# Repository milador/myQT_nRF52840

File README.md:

# myQT_nRF52840

myQT nRF52840 is a development board based on Nordic nRF52840 Bluetooth module in Seeeduino XIAO/QT py form factor.

## myQT nRF52840 Arduino IDE Setup

Please visit [milador-arduino](https://github.com/milador/milador-arduino/blob/main/boards/README.md) github page to find out about installation process.

## myQT nRF52840 Pinout

## myQT nRF52840 PCB Design 

## myQT nRF52840 3D Model

## License

Designed by milador based on Adafruit QT py design.

Creative Commons Attribution/Share-Alike, all text above must be included in any redistribution. Please read license.txt for additional details.

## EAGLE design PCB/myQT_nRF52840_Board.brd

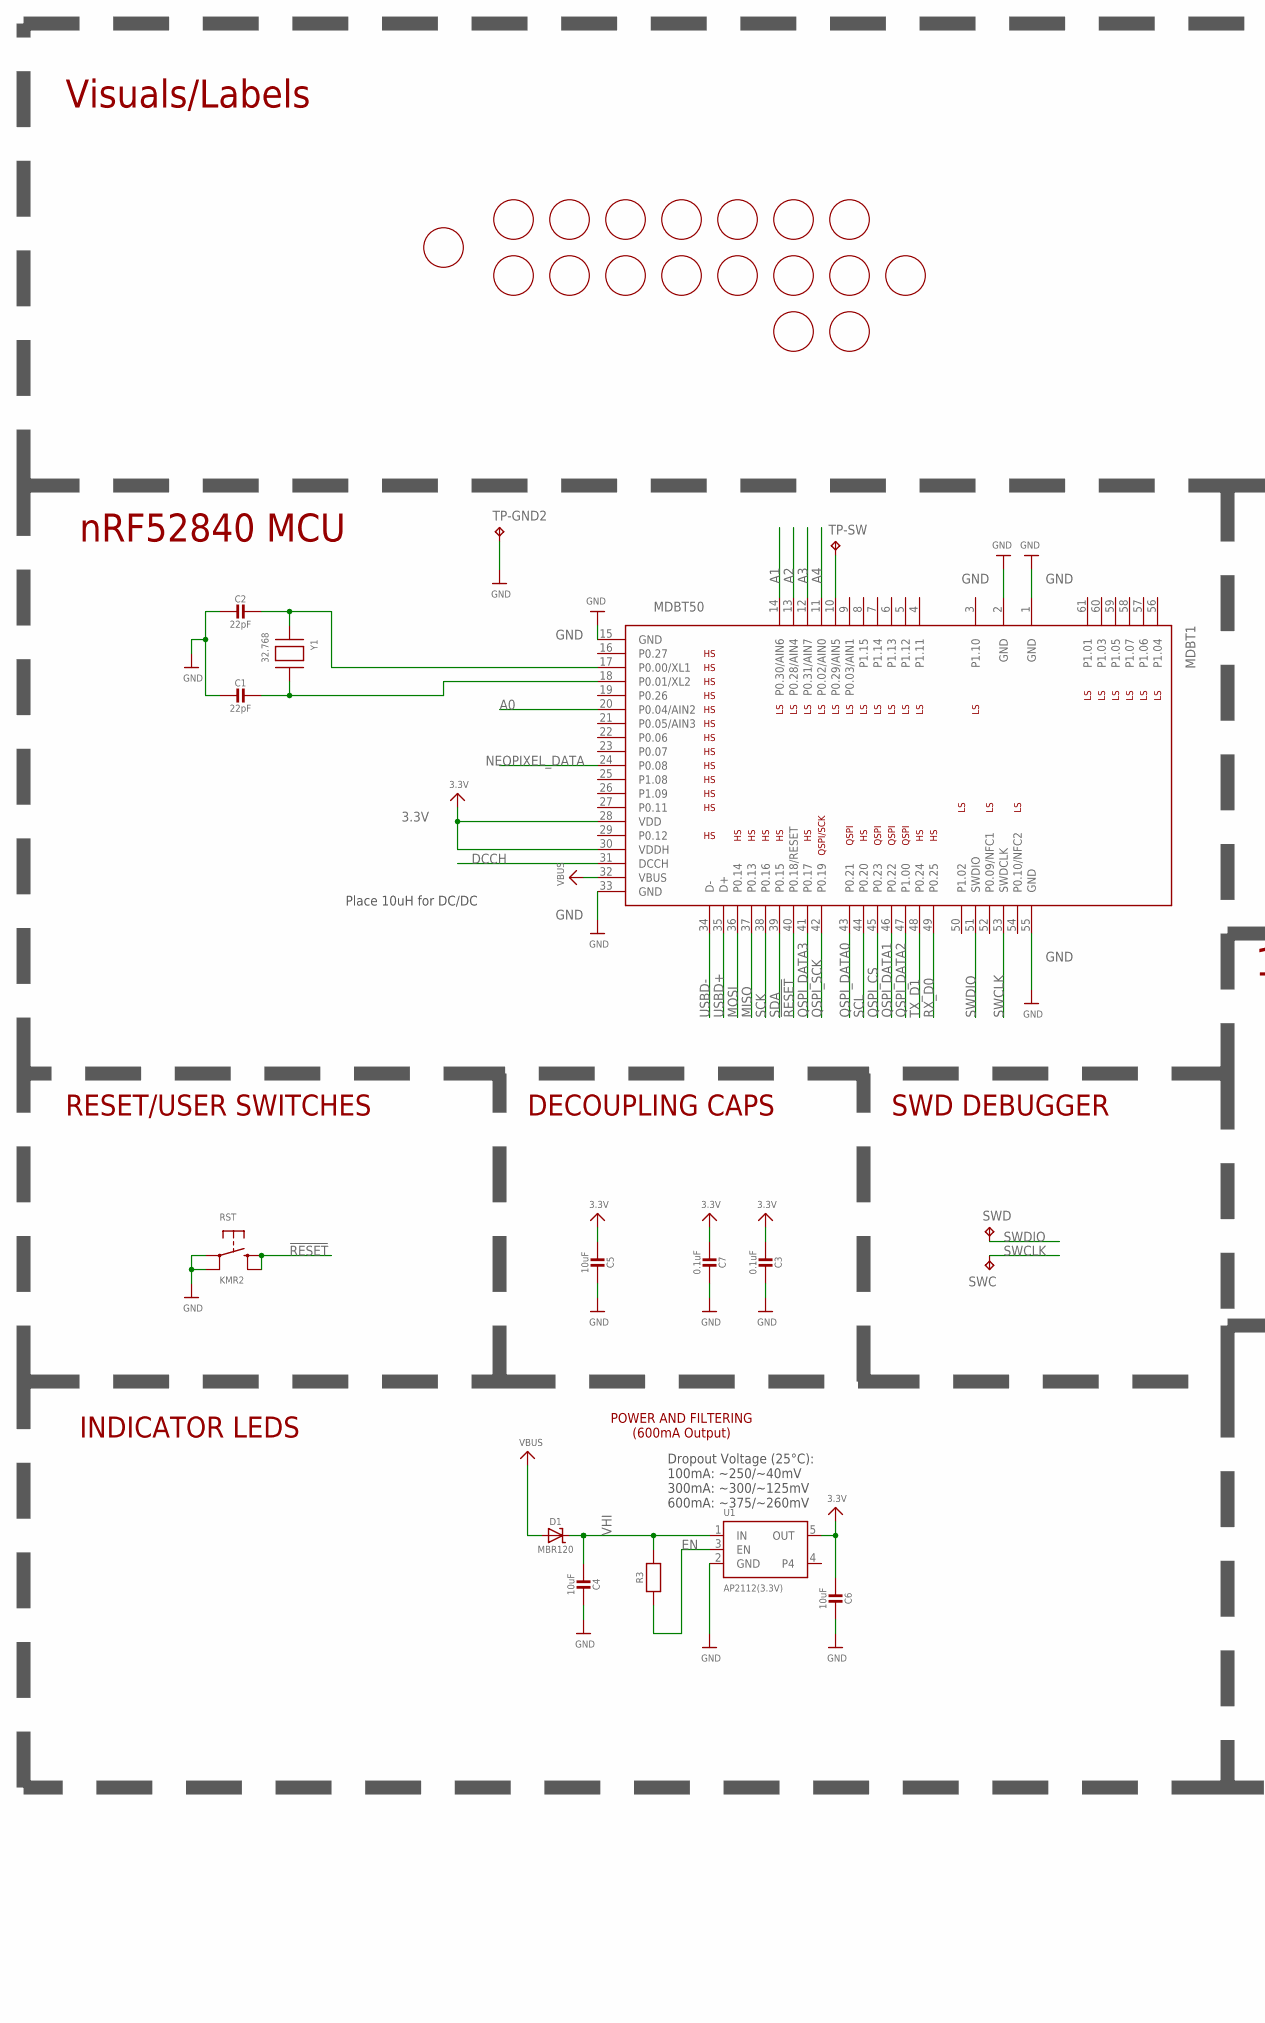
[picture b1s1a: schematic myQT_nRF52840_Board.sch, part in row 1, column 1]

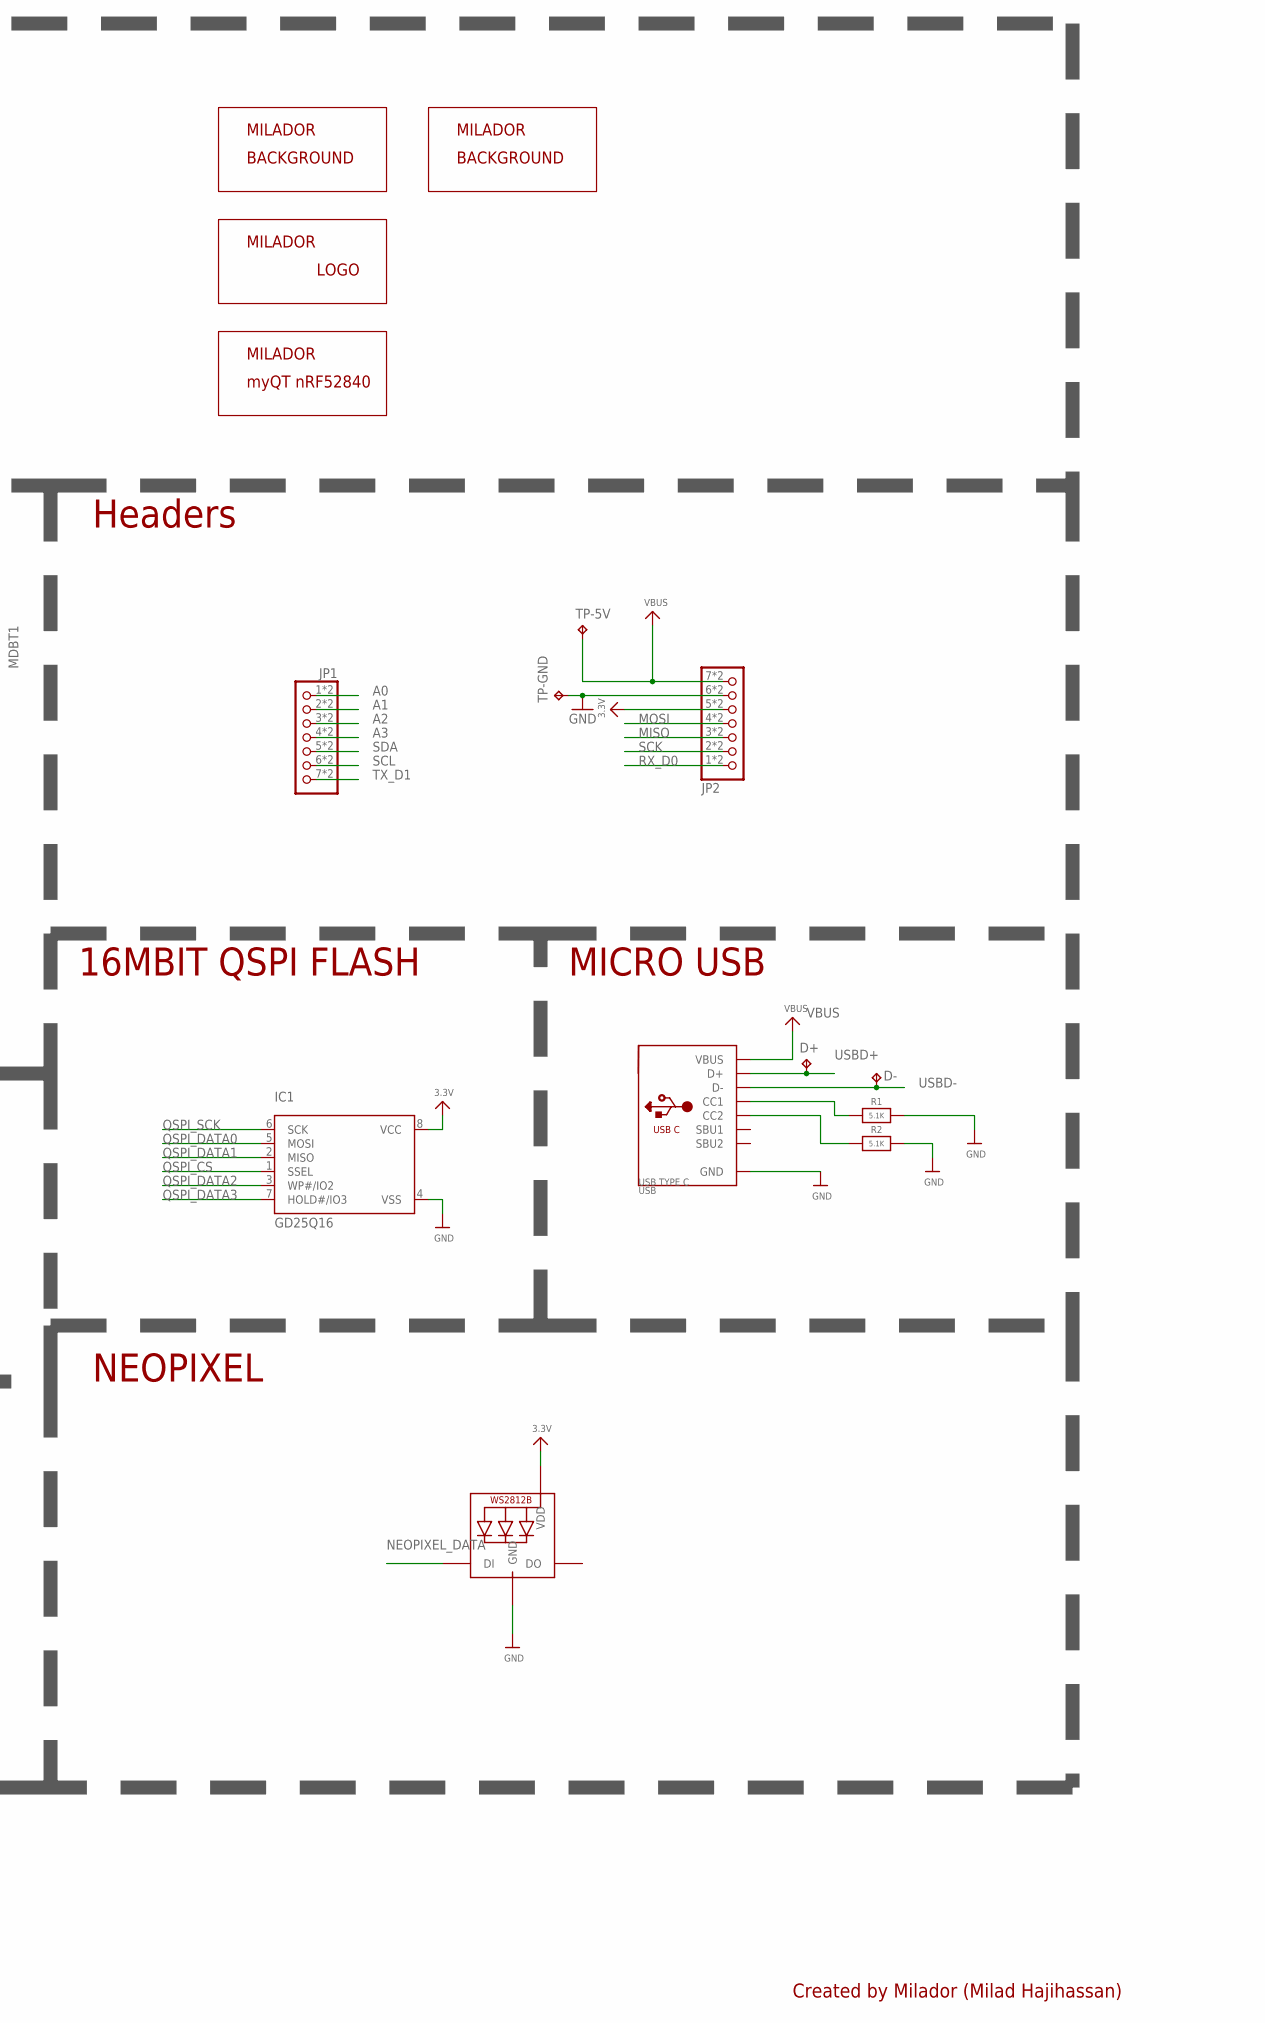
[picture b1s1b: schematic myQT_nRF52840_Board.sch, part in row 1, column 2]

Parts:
C1, C2: 22pF; 0603-MP
C3, C7: 0.1uF; 0603-NO
C4, C5, C6: 10uF; 0805-NO
D1: MBR120; SOD-123
D+: TESTPAD_TPTP10R; TESTPAD_TP10R
D-: TESTPAD_TPTP10R; TESTPAD_TP10R
IC1: GD25Q16; USON8
JP1, JP2: HEADER-1X7_CASTEL; 1X07_CASTEL
LED: WS2812B_SK6805_1515; SK6805_1515
MDBT1: MDBT50
R1, R2: 5.1K; 0402-NO
R3: 10K; 0603-NO
RST: KMR2; BTN_KMR2_4.6X2.8
SWC: TESTPAD_TPTP13R; TESTPAD_TP13R
SWD: TESTPAD_TPTP13R; TESTPAD_TP13R
TP-5V: TESTPAD_TPB1,27; TESTPAD_B1,27
TP-GND: TESTPAD_TPB1,27; TESTPAD_B1,27
TP-GND2: TESTPAD_TPTP06R; TESTPAD_TP06R
TP-SW: TESTPAD_TPTP06R; TESTPAD_TP06R
U1: AP2112(3.3V); SOT23-5
U$6: MILADOR-PIN-NAME-A0; PIN-A0
U$7: MILADOR-PIN-NAME-5V; PIN-5V
U$10: MILADOR-PIN-NAME-GND; PIN-GND
U$12: MILADOR-PIN-NAME-3V; PIN-3V
U$14: MILADOR-PIN-NAME-MO2; PIN-MO2
U$18: MILADOR-PIN-NAME-MI2; PIN-MI2
U$20: MILADOR-PIN-NAME-SCK2; PIN-SCK2
U$24: MILADOR-PIN-NAME-RX; PIN-RX
U$25: MILADOR-PIN-NAME-A1; PIN-A1
U$26: MILADOR-PIN-NAME-A2; PIN-A2
U$27: MILADOR-PIN-NAME-A3; PIN-A3
U$28: MILADOR-PIN-NAME-TX; PIN-TX
U$29: MILADOR-PIN-NAME-SDA2; PIN-SDA2
U$33: MILADOR-PIN-NAME-SCL2; PIN-SCL2
U$36: MILADOR-PIN-NAME-RST; PIN-RST
U$37: MILADOR-BACKGROUND-VANCOUVER; MILADOR_BG_VAN
U$38: MILADOR-DEVICE-; MILADOR_MYQT_NRF52840
U$39: MILADOR-LOGO-; MILADOR_LOGO1
U$40: MILADOR-BACKGROUND-CANADA_SM; MILADOR_BG_CAN_SM
U$41: MILADOR-PIN-NAME-D+; PIN-D+
U$43: MILADOR-PIN-NAME-D-; PIN-D-
U$44: MILADOR-PIN-NAME-SW; PIN-SW
USB: USB TYPE C; USB_C_CUSB31-CFM2AX-01-X
Y1: 32.768; ADAFRUIT2_XTAL3215

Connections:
3.3V: C3.2, C5.2, C6.2, C7.2, IC1.8 (VCC), JP2.5, JP2.5C (5), LED.2 (VDD), MDBT1.28 (VDD), MDBT1.30 (VDDH), U1.5 (OUT)
!RESET: MDBT1.40 (P0.18/RESET), RST.B (S), RST.B' (S1)
A0: JP1.1, JP1.1C (1), MDBT1.20 (P0.04/AIN2)
A1: JP1.2, JP1.2C (2), MDBT1.14 (P0.30/AIN6)
A2: JP1.3, JP1.3C (3), MDBT1.13 (P0.28/AIN4)
A3: JP1.4, JP1.4C (4), MDBT1.12 (P0.31/AIN7)
A4: MDBT1.11 (P0.02/AIN0)
DCCH: MDBT1.31 (DCCH)
EN: R3.1, U1.3 (EN)
GND: C1.2, C2.2, C3.1, C4.1, C5.1, C6.1, C7.1, IC1.4 (VSS), JP2.6, JP2.6C (6), LED.4 (GND), MDBT1.1 (GND), MDBT1.2 (GND), MDBT1.15 (GND), MDBT1.33 (GND), MDBT1.55 (GND), R1.2, R2.2, RST.A, RST.A' (P1), TP-GND.TP, TP-GND2.TP, U1.2 (GND), USB.A1B12 (GND), USB.B1A12 (GND)
MISO: JP2.3, JP2.3C (3), MDBT1.37 (P0.13)
MOSI: JP2.4, JP2.4C (4), MDBT1.36 (P0.14)
unnamed: MDBT1.10 (P0.29/AIN5), TP-SW.TP
unnamed: R1.1, USB.A5 (CC1)
unnamed: R2.1, USB.B5 (CC2)
unnamed: C2.1, MDBT1.17 (P0.00/XL1), Y1.P$1
unnamed: C1.1, MDBT1.18 (P0.01/XL2), Y1.P$2
NEOPIXEL_DATA: LED.1 (DI), MDBT1.24 (P0.08)
QSPI_CS: IC1.1 (SSEL), MDBT1.45 (P0.23)
QSPI_DATA0: IC1.5 (MOSI), MDBT1.43 (P0.21)
QSPI_DATA1: IC1.2 (MISO), MDBT1.46 (P0.22)
QSPI_DATA2: IC1.3 (WP#/IO2), MDBT1.47 (P1.00)
QSPI_DATA3: IC1.7 (HOLD#/IO3), MDBT1.41 (P0.17)
QSPI_SCK: IC1.6 (SCK), MDBT1.42 (P0.19)
RX_D0: JP2.1, JP2.1C (1), MDBT1.49 (P0.25)
SCK: JP2.2, JP2.2C (2), MDBT1.38 (P0.16)
SCL: JP1.6, JP1.6C (6), MDBT1.44 (P0.20)
SDA: JP1.5, JP1.5C (5), MDBT1.39 (P0.15)
SWCLK: MDBT1.53 (SWDCLK), SWC.TP
SWDIO: MDBT1.51 (SWDIO), SWD.TP
TX_D1: JP1.7, JP1.7C (7), MDBT1.48 (P0.24)
USBD+: D+.TP, MDBT1.35 (D+), USB.A6 (D+), USB.B6 (D+)
USBD-: D-.TP, MDBT1.34 (D-), USB.A7 (D-), USB.B7 (D-)
VBUS: D1.A, JP2.7, JP2.7C (7), MDBT1.32 (VBUS), TP-5V.TP, USB.A4B9 (VBUS), USB.B4A9 (VBUS)
VHI: C4.2, D1.C, R3.2, U1.1 (IN)

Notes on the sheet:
POWER AND FILTERING (600mA Output)
Dropout Voltage (25°C): 100mA: ~250/~40mV 300mA: ~300/~125mV 600mA: ~375/~260mV
INDICATOR LEDS
RESET/USER SWITCHES
DECOUPLING CAPS
SWD DEBUGGER
16MBIT QSPI FLASH
MICRO USB
Place 10uH for DC/DC
Created by Milador (Milad Hajihassan)
Headers
nRF52840 MCU
Visuals/Labels
NEOPIXEL

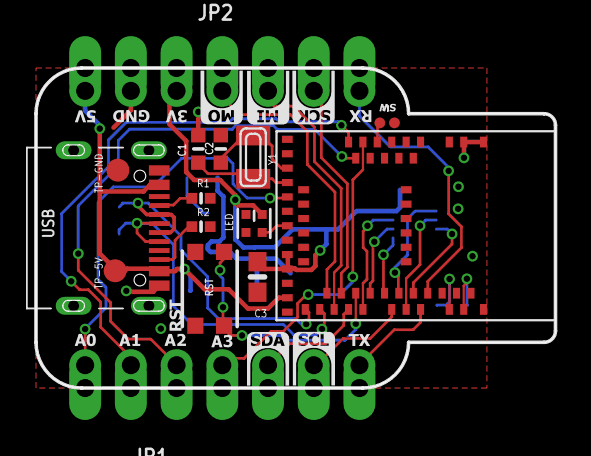
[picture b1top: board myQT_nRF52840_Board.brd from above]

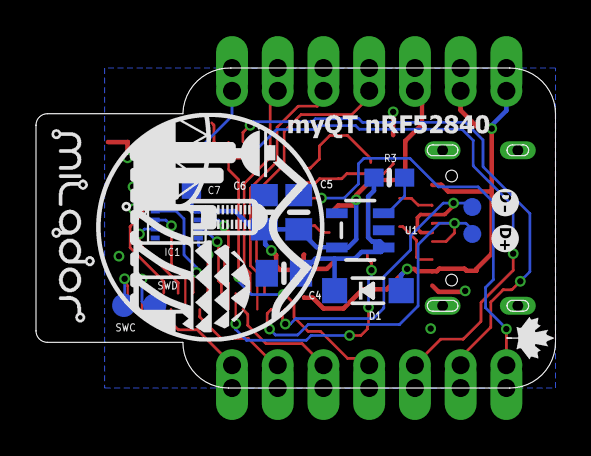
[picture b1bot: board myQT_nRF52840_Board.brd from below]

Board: 2 copper layers, 28.9 x 17.8 mm, 50 parts (18 on the bottom side), 33 nets.

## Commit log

2021-12-05 Added PCB files
2021-12-05 Added Images
2021-12-06 Updated Pinout picture
2021-12-06 Updated PCB image
2021-12-06 Updated pinout link
2022-03-12 Updated instructions

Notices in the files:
parts and their libraries:
microbuilder: This work is placed in the public domain, and may be freely used for commercial and non-commercial work with the following conditions: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
